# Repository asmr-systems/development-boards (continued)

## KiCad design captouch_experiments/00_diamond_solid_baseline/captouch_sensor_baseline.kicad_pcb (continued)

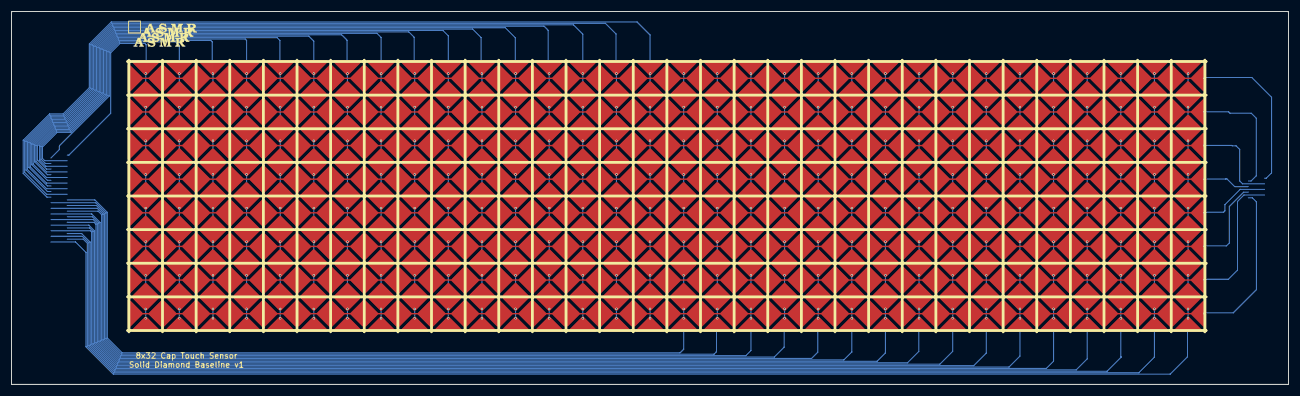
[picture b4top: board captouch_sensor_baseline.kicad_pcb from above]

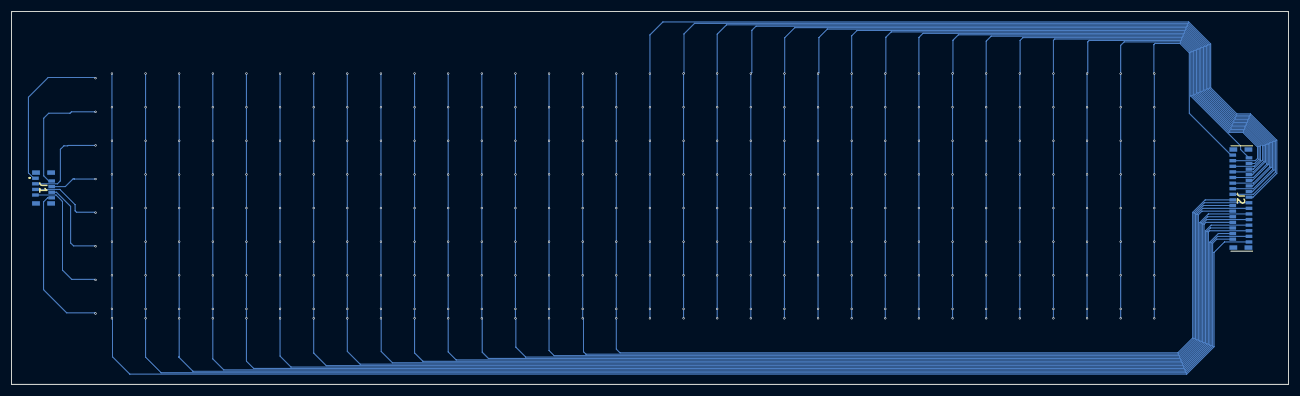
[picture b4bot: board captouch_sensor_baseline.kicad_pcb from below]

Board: 2 copper layers, 227.9 x 66.5 mm, 3 parts (2 on the bottom side), 40 nets.
